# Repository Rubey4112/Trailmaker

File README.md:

# Reactor
A game designed for Hackclub Pathfinder YSWS.

## Description
Reactor is a high score reaction game were the player have to click the corresponding button indicated by the LED within a set amount of time (configurable by the game difficulty) else the reactor explodes (i.e. you lose). Think of it as pocketable Bop It that you can pull out when you're bored.

## PCB schematic

## PCB layout

## PCB front

## PCB back

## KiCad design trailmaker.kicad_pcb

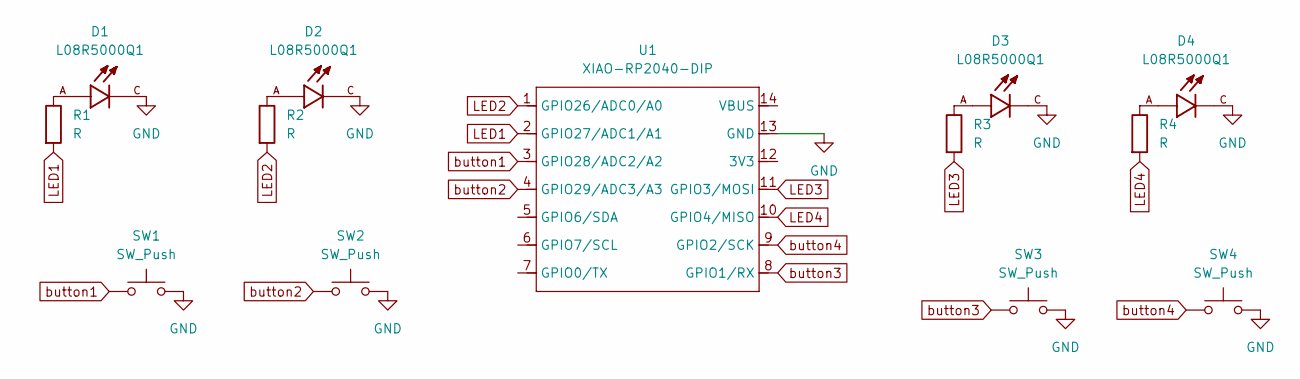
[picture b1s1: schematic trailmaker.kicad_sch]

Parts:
D1, D2, D3, D4: L08R5000Q1; LEDRD254W57D500H1070; PARTREV NA
R1, R2, R3, R4: R; R_Axial_DIN0204_L3.6mm_D1.6mm_P5.08mm_Horizontal
SW1, SW2, SW3, SW4: SW_Push; SW_Cherry_MX_1.00u_PCB_Rubey
U1: XIAO-RP2040-DIP

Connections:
GND: D1.C, D2.C, D3.C, D4.C, SW1.2, SW2.2, SW3.2, SW4.2, U1.13 (GND)
LED1: R1.2, U1.2 (GPIO27/ADC1/A1)
LED2: R2.2, U1.1 (GPIO26/ADC0/A0)
LED3: R3.2, U1.11 (GPIO3/MOSI)
LED4: R4.2, U1.10 (GPIO4/MISO)
unnamed: D1.A, R1.1
unnamed: D2.A, R2.1
unnamed: D3.A, R3.1
unnamed: D4.A, R4.1
button1: SW1.1, U1.3 (GPIO28/ADC2/A2)
button2: SW2.1, U1.4 (GPIO29/ADC3/A3)
button3: SW3.1, U1.8 (GPIO1/RX)
button4: SW4.1, U1.9 (GPIO2/SCK)

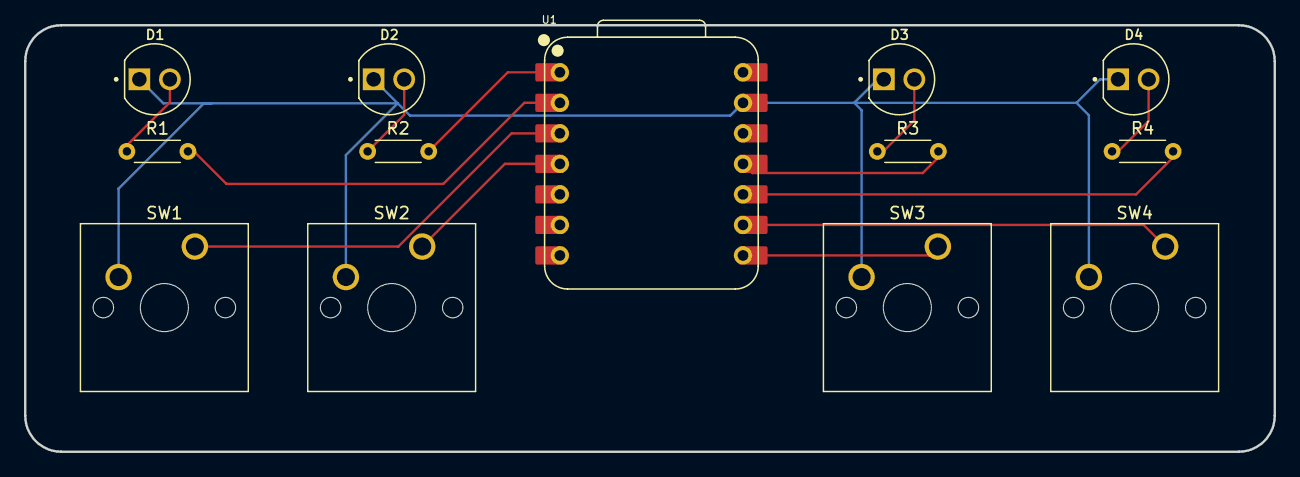
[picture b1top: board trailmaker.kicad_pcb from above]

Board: 2 copper layers, 104.0 x 35.5 mm, 13 parts (0 on the bottom side), 13 nets.

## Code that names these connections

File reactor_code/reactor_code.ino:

#include <Bounce2.h>

/* Xiao RP20240 */
const int BUT1 = D2;
const int BUT2 = D3;
const int BUT3 = D7;
const int BUT4 = D8;

const int LED1 = D0;
const int LED2 = D1;
const int LED3 = D10;
const int LED4 = D9;

/* Wokwi Simulator */
// const int BUT1 = 8;
// const int BUT2 = 9;
// const int BUT3 = 21;
// const int BUT4 = 22;

// const int LED1 = 6;
// const int LED2 = 7;
// const int LED3 = 26;
// const int LED4 = 27;

const int button_pin_array[4] = {BUT1, BUT2, BUT3, BUT4};
Bounce2::Button *button_array = new Bounce2::Button[4];

const int led_array[4] = {LED1, LED2, LED3, LED4};

bool start = false;
int difficulty = 0; // 0-9
bool loose = false;
int level = 0;
bool lights_on = false;

typedef struct
{
  int indicator; // indicate the button the player must press to move on
  unsigned long prev_time;
  int led_on_duration;
  bool has_run;
  int round_start_delay;
} RoundData; // data set here will only be set once per round

/*
  indicator, prev_time, duration, has_run
*/
RoundData round_data = {0, 0, 0, false, 0};

void setup()
{
  Serial1.begin(9600);
  for (int i = 0; i < 4; i++)
  {
    button_array[i].attach(button_pin_array[i], INPUT_PULLUP);
    button_array[i].interval(5);
    button_array[i].setPressedState(LOW);
  }

  pinMode(LED1, OUTPUT);
  pinMode(LED2, OUTPUT);
  pinMode(LED3, OUTPUT);
  pinMode(LED4, OUTPUT);

  randomSeed(analogRead(A0));
}

/*
  Buttons layout
  1 2 3 4
*/

/*
  1 + 4 = Start game
  2 decrease difficulty
  3 increase difficulty

  1 view previous high score
  4 change game mode
*/
void game_menu()
{
  // Serial1.println("menu");
  if (button_array[0].isPressed() && button_array[3].isPressed())
  {
    start = true;
  }
  /* To be implemented in the future */
  // if (button_array[1].pressed())
  // {
  //   difficulty--;
  // }
  // if (button_array[2].pressed())
  // {
  //   difficulty++;
  // }
}

/*
  reset global val and display score
*/
void game_loose()
{
  // Serial1.println("game loose");
  start = false;
  loose = false;
  difficulty = 0;
  round_data = {0, 0, 0, false, 0};

  for (int i = 0; i < 3; i++)
  {
    digitalWrite(LED1, HIGH);
    digitalWrite(LED2, HIGH);
    digitalWrite(LED3, HIGH);
    digitalWrite(LED4, HIGH);
    delay(300);
    digitalWrite(LED1, LOW);
    digitalWrite(LED2, LOW);
    digitalWrite(LED3, LOW);
    digitalWrite(LED4, LOW);
    delay(300);
  }
  delay(500);

  // ten digit
  for (int i = level / 10; i > 0; i--)
  {
    digitalWrite(LED1, HIGH);
    digitalWrite(LED2, HIGH);
    delay(400);
    digitalWrite(LED1, LOW);
    digitalWrite(LED2, LOW);
    delay(400);
  }

  delay(500);

  // one digit
  for (int i = level % 10; i > 0; i--)
  {
    digitalWrite(LED3, HIGH);
    digitalWrite(LED4, HIGH);
    delay(400);
    digitalWrite(LED3, LOW);
    digitalWrite(LED4, LOW);
    delay(400);
  }

  level = 0;
}

/*
  delay decreases slowly but eventually get fast and then slow again
  using a precalculated table
*/
const int duration_table[10] = {3000, 2720, 2668, 2540, 2350, 2000, 1400, 1325, 1320, 1300};
int get_duration(int difficulty)
{
  return difficulty < 10 ? duration_table[difficulty] : duration_table[9];
}

int get_delay()
{
  return int(random(200, 2000));
}

void new_round_helper(int difficulty)
{
  round_data = {random(4), millis(), get_duration(difficulty), true, get_delay()};
}

/*
  This function should only be called once at the start of every round
*/
void new_round(int difficulty)
{
  if (!round_data.has_run)
  {
    new_round_helper(difficulty);
  }
}

/*
  if button pressed and indicator on -> next round
  if button pressed and indicator off -> you loose
  if timer ran out -> you loose
  every level the difficulty increase
*/
void game_loop()
{
  new_round(difficulty);
  unsigned long curr_time = millis();

  // game loose if button is press at the beginning round delay
  if (curr_time - round_data.prev_time < round_data.round_start_delay)
  {
    // Serial1.println("delay");
    for (int i = 0; i < 4; i++)
    {
      if (button_array[i].pressed())
      {
        loose = true;
      }
    }
  }
  else
  {
    if (!loose && curr_time - round_data.prev_time < round_data.led_on_duration + round_data.round_start_delay)
    {
      digitalWrite(led_array[round_data.indicator], HIGH);
      for (int i = 0; i < 4; i++)
      {
        if (button_array[i].pressed())
        {
          if (i == round_data.indicator)
          {
            difficulty++;
            level++;
            round_data.has_run = false;
            digitalWrite(led_array[round_data.indicator], LOW);
          }
          else
          {
            loose = true;
          }
        }
      }
    }
    else
    {
      loose = true;
    }
  }
}

void test_mode()
{
  for (int i = 0; i < 4; i++)
  {
    if (button_array[i].isPressed())
    {
      digitalWrite(led_array[i], HIGH);
    }
    else
    {
      digitalWrite(led_array[i], LOW);
    }
  }
}

void led_test_mode()
{
  for (int i = 0; i < 4; i++)
  {
    digitalWrite(led_array[i], HIGH);
    delay(1000);
    digitalWrite(led_array[i], LOW);
    delay(1000);
  }
}

void update_buttons()
{
  for (int i = 0; i < 4; i++)
  {
    button_array[i].update();
  }
}

void loop()
{
  update_buttons();
  delay(1); // for wokwi simulation so it doesn't lag

#ifdef TESTMODE
  test_mode();
#endif

#ifndef TESTMODE
  if (start)
  {
    if (loose)
    {
      game_loose();
    }
    else
    {
      game_loop();
    }
  }
  else
  {
    game_menu();
  }
#endif
}

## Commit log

2025-06-29 created PCB layout and Arduino code
2025-06-30 prototyping of the game loop
2025-07-01 Got code to compiled.
2025-07-01 added test mode
    use to test the buttons and leds
2025-07-04 Code bug fixing and PCB finalization
    Added silkscreen to PCB and exported gerber and dril file for JLC PCB
2025-07-04 Added PCB images
2025-07-05 Refactored arduino code to work with PlatformIO Needed to use Wokwi interactive debugger
2025-07-05 Fixed game logic
2025-07-05 remove unused features
2025-07-05 updated code to work with Xiao RP2040
2025-08-14 added banner for summer of making
